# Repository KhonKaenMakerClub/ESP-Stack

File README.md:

# ESP-Stack
ESP8266 hardware and software framework

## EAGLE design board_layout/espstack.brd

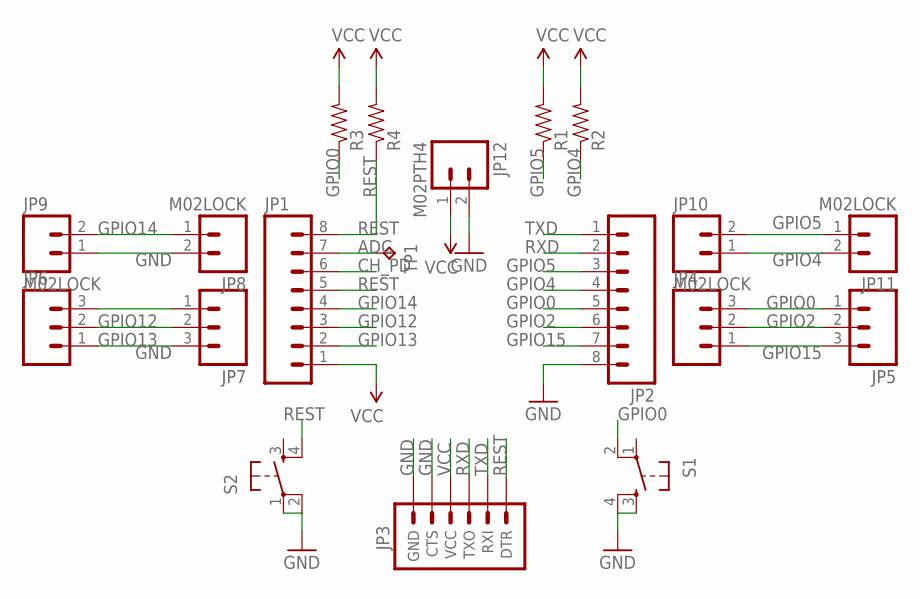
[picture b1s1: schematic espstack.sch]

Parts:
JP1, JP2: M08LOCK_LONGPADS; 1X08_LOCK_LONGPADS
JP3: ARDUINO_SERIAL_PROGRAMLOCK; 1X06_LOCK
JP4, JP5, JP6, JP7: M03LOCK; 1X03_LOCK
JP8, JP9, JP10, JP11: M02LOCK; 1X02_LOCK
JP12: M02PTH4; 1X02_XTRA_BIG
R1, R2, R3, R4: RESISTOR0805-RES; 0805
S1, S2: TAC_SWITCHPTH; TACTILE-PTH
TP1: TPB2,54; B2,54

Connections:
ADC: JP1.7, TP1.TP
CH_PD: JP1.6
GND: JP2.8, JP3.5 (CTS), JP3.6 (GND), JP6.1, JP7.3, JP8.2, JP9.1, JP12.2, S1.3, S1.4, S2.1, S2.2
GPIO0: JP2.5, JP4.3, JP5.1, R3.1, S1.2
GPIO2: JP2.6, JP4.2, JP5.2
GPIO4: JP2.4, JP10.1, JP11.2, R2.1
GPIO5: JP2.3, JP10.2, JP11.1, R1.1
GPIO12: JP1.3, JP6.3, JP7.1
GPIO13: JP1.2, JP6.2, JP7.2
GPIO14: JP1.4, JP8.1, JP9.2
GPIO15: JP2.7, JP4.1, JP5.3
REST: JP1.5, JP1.8, JP3.1 (DTR), R4.1, S2.4
RXD: JP2.2, JP3.3 (TXO)
TXD: JP2.1, JP3.2 (RXI)
VCC: JP1.1, JP3.4 (VCC), JP12.1, R1.2, R2.2, R3.2, R4.2

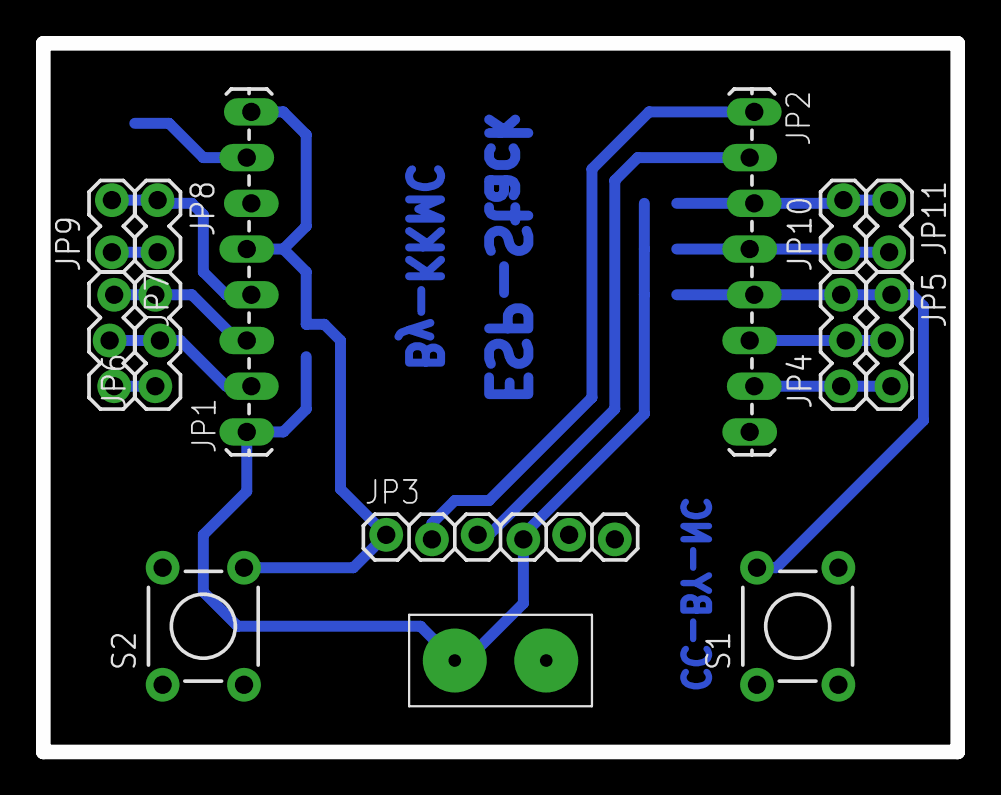
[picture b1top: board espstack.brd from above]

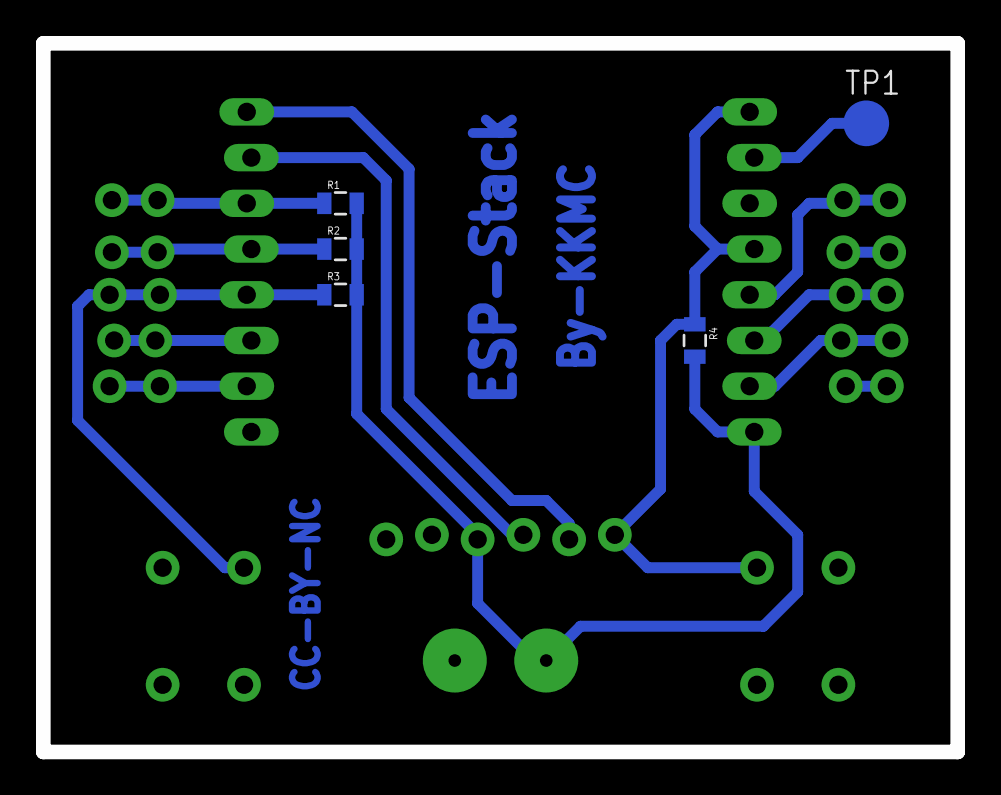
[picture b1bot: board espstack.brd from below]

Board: 2 copper layers, 50.8 x 39.4 mm, 20 parts (5 on the bottom side), 14 nets.

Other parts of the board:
U$3: A4-35SC

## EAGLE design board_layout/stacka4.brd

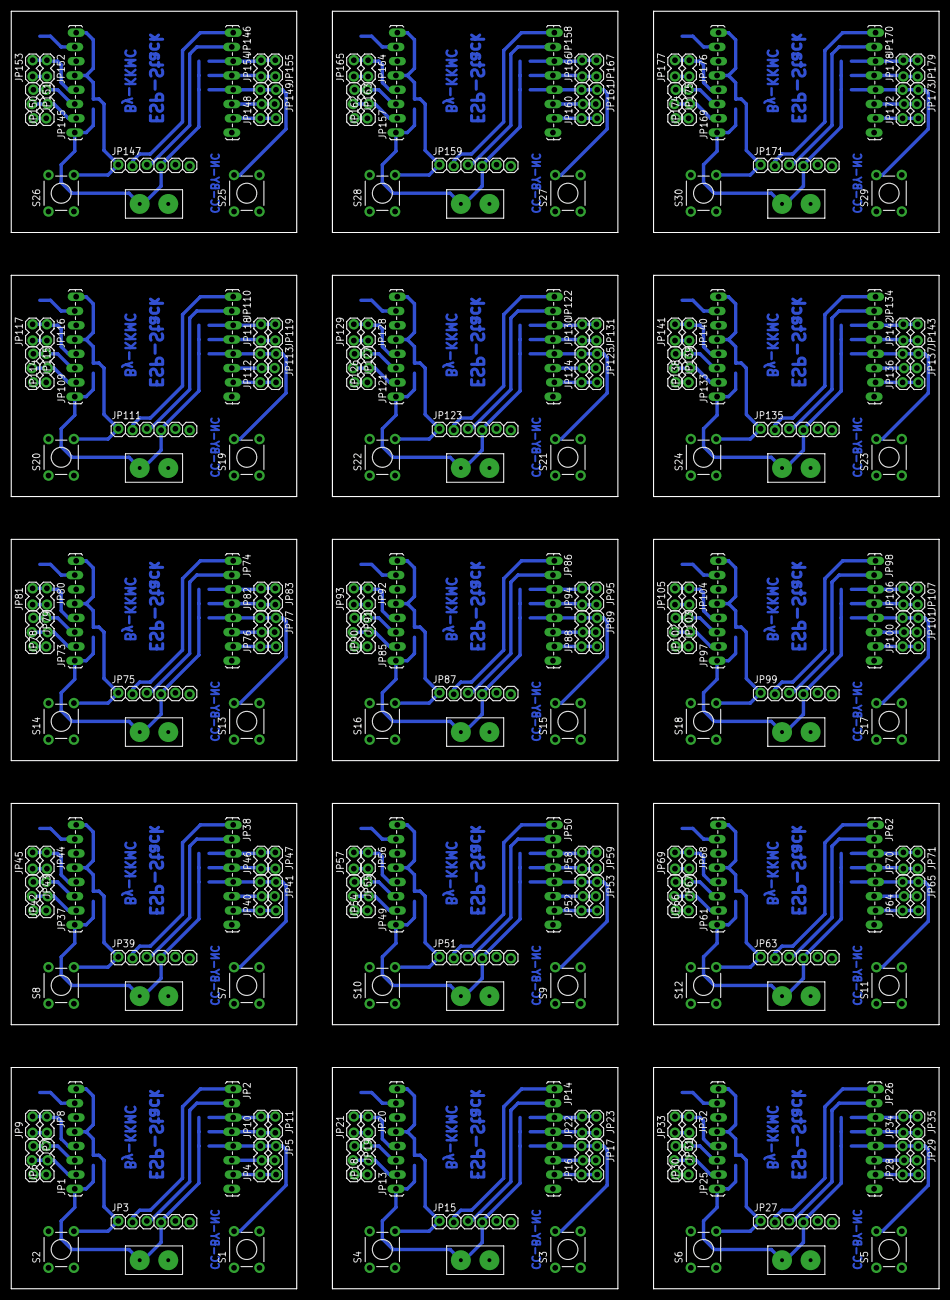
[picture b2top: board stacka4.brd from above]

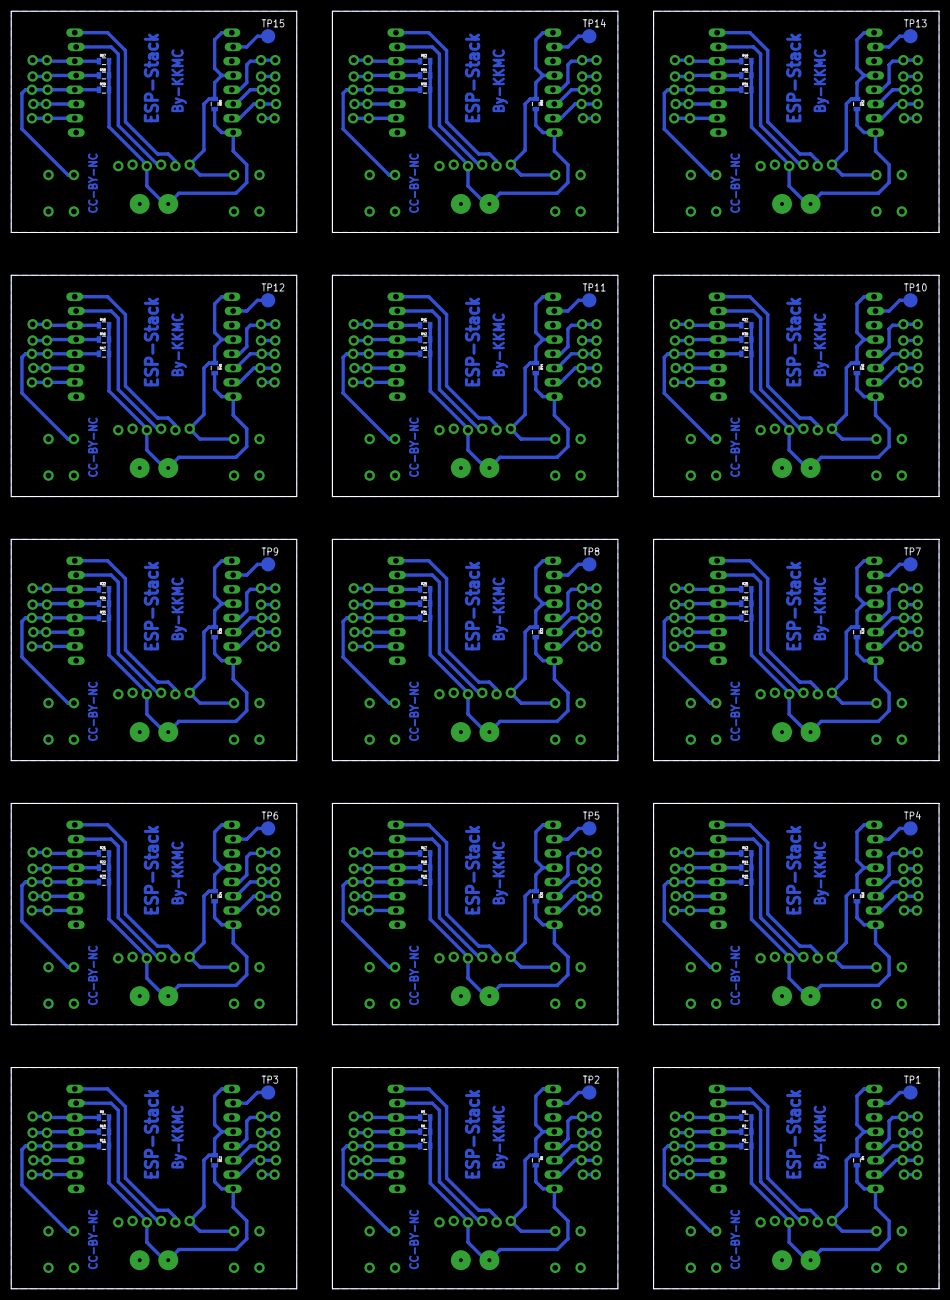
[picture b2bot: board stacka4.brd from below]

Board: 2 copper layers, 165.1 x 227.3 mm, 286 parts (75 on the bottom side), 210 nets.

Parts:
E$1: A4-35SC
JP1, JP2, JP13, JP14, JP25, JP26, JP37, JP38, JP49, JP50, JP61, JP62, JP73, JP74, JP85, JP86, JP97, JP98, JP109, JP110, JP121, JP122, JP133, JP134, JP145, JP146, JP157, JP158, JP169, JP170: 1X08_LOCK_LONGPADS
JP3, JP15, JP27, JP39, JP51, JP63, JP75, JP87, JP99, JP111, JP123, JP135, JP147, JP159, JP171: 1X06_LOCK
JP4, JP5, JP6, JP7, JP16, JP17, JP18, JP19, JP28, JP29, JP30, JP31, JP40, JP41, JP42, JP43, JP52, JP53, JP54, JP55, JP64, JP65, JP66, JP67, JP76, JP77, JP78, JP79, JP88, JP89, JP90, JP91, JP100, JP101, JP102, JP103, JP112, JP113, JP114, JP115, JP124, JP125, JP126, JP127, JP136, JP137, JP138, JP139, JP148, JP149, JP150, JP151, JP160, JP161, JP162, JP163, JP172, JP173, JP174, JP175: 1X03_LOCK
JP8, JP9, JP10, JP11, JP20, JP21, JP22, JP23, JP32, JP33, JP34, JP35, JP44, JP45, JP46, JP47, JP56, JP57, JP58, JP59, JP68, JP69, JP70, JP71, JP80, JP81, JP82, JP83, JP92, JP93, JP94, JP95, JP104, JP105, JP106, JP107, JP116, JP117, JP118, JP119, JP128, JP129, JP130, JP131, JP140, JP141, JP142, JP143, JP152, JP153, JP154, JP155, JP164, JP165, JP166, JP167, JP176, JP177, JP178, JP179: M02LOCK; 1X02_LOCK
JP12, JP24, JP36, JP48, JP60, JP72, JP84, JP96, JP108, JP120, JP132, JP144, JP156, JP168, JP180: M02PTH4; 1X02_XTRA_BIG
R1, R2, R3, R4, R5, R6, R7, R8, R9, R10, R11, R12, R13, R14, R15, R16, R17, R18, R19, R20, R21, R22, R23, R24, R25, R26, R27, R28, R29, R30, R31, R32, R33, R34, R35, R36, R37, R38, R39, R40, R41, R42, R43, R44, R45, R46, R47, R48, R49, R50, R51, R52, R53, R54, R55, R56, R57, R58, R59, R60: 0805
S1, S2, S3, S4, S5, S6, S7, S8, S9, S10, S11, S12, S13, S14, S15, S16, S17, S18, S19, S20, S21, S22, S23, S24, S25, S26, S27, S28, S29, S30: TACTILE-PTH
TP1, TP2, TP3, TP4, TP5, TP6, TP7, TP8, TP9, TP10, TP11, TP12, TP13, TP14, TP15: TPB2,54; B2,54

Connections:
ADC: JP1.7, TP1.TP
ADC1: JP13.7, TP2.TP
ADC2: JP25.7, TP3.TP
ADC3: JP37.7, TP4.TP
ADC4: JP49.7, TP5.TP
ADC5: JP61.7, TP6.TP
ADC6: JP73.7, TP7.TP
ADC7: JP85.7, TP8.TP
ADC8: JP97.7, TP9.TP
ADC9: JP109.7, TP10.TP
ADC10: JP121.7, TP11.TP
ADC11: JP133.7, TP12.TP
ADC12: JP145.7, TP13.TP
ADC13: JP157.7, TP14.TP
ADC14: JP169.7, TP15.TP
GND: JP2.8, JP3.5, JP3.6, JP6.1, JP7.3, JP8.2, JP9.1, JP12.2, S1.3, S1.4, S2.1, S2.2
GND1: JP14.8, JP15.5, JP15.6, JP18.1, JP19.3, JP20.2, JP21.1, JP24.2, S3.3, S3.4, S4.1, S4.2
GND2: JP26.8, JP27.5, JP27.6, JP30.1, JP31.3, JP32.2, JP33.1, JP36.2, S5.3, S5.4, S6.1, S6.2
GND3: JP38.8, JP39.5, JP39.6, JP42.1, JP43.3, JP44.2, JP45.1, JP48.2, S7.3, S7.4, S8.1, S8.2
GND4: JP50.8, JP51.5, JP51.6, JP54.1, JP55.3, JP56.2, JP57.1, JP60.2, S9.3, S9.4, S10.1, S10.2
GND5: JP62.8, JP63.5, JP63.6, JP66.1, JP67.3, JP68.2, JP69.1, JP72.2, S11.3, S11.4, S12.1, S12.2
GND6: JP74.8, JP75.5, JP75.6, JP78.1, JP79.3, JP80.2, JP81.1, JP84.2, S13.3, S13.4, S14.1, S14.2
GND7: JP86.8, JP87.5, JP87.6, JP90.1, JP91.3, JP92.2, JP93.1, JP96.2, S15.3, S15.4, S16.1, S16.2
GND8: JP98.8, JP99.5, JP99.6, JP102.1, JP103.3, JP104.2, JP105.1, JP108.2, S17.3, S17.4, S18.1, S18.2
GND9: JP110.8, JP111.5, JP111.6, JP114.1, JP115.3, JP116.2, JP117.1, JP120.2, S19.3, S19.4, S20.1, S20.2
GND10: JP122.8, JP123.5, JP123.6, JP126.1, JP127.3, JP128.2, JP129.1, JP132.2, S21.3, S21.4, S22.1, S22.2
GND11: JP134.8, JP135.5, JP135.6, JP138.1, JP139.3, JP140.2, JP141.1, JP144.2, S23.3, S23.4, S24.1, S24.2
GND12: JP146.8, JP147.5, JP147.6, JP150.1, JP151.3, JP152.2, JP153.1, JP156.2, S25.3, S25.4, S26.1, S26.2
GND13: JP158.8, JP159.5, JP159.6, JP162.1, JP163.3, JP164.2, JP165.1, JP168.2, S27.3, S27.4, S28.1, S28.2
GND14: JP170.8, JP171.5, JP171.6, JP174.1, JP175.3, JP176.2, JP177.1, JP180.2, S29.3, S29.4, S30.1, S30.2
GPIO0: JP2.5, JP4.3, JP5.1, R3.1, S1.2
GPIO1: JP13.4, JP20.1, JP21.2
GPIO2: JP2.6, JP4.2, JP5.2
GPIO3: JP13.3, JP18.3, JP19.1
GPIO4: JP2.4, JP10.1, JP11.2, R2.1
GPIO5: JP2.3, JP10.2, JP11.1, R1.1
GPIO6: JP13.2, JP18.2, JP19.2
GPIO7: JP14.7, JP16.1, JP17.3
GPIO8: JP14.6, JP16.2, JP17.2
GPIO9: JP14.5, JP16.3, JP17.1, R7.1, S3.2
GPIO10: JP14.4, JP22.1, JP23.2, R6.1
GPIO11: JP14.3, JP22.2, JP23.1, R5.1
GPIO12: JP1.3, JP6.3, JP7.1
GPIO13: JP1.2, JP6.2, JP7.2
GPIO14: JP1.4, JP8.1, JP9.2
GPIO15: JP2.7, JP4.1, JP5.3
GPIO16: JP25.4, JP32.1, JP33.2
GPIO17: JP25.3, JP30.3, JP31.1
GPIO18: JP25.2, JP30.2, JP31.2
GPIO19: JP26.7, JP28.1, JP29.3
GPIO20: JP26.6, JP28.2, JP29.2
GPIO21: JP26.5, JP28.3, JP29.1, R11.1, S5.2
GPIO22: JP26.4, JP34.1, JP35.2, R10.1
GPIO23: JP26.3, JP34.2, JP35.1, R9.1
GPIO24: JP37.4, JP44.1, JP45.2
GPIO25: JP37.3, JP42.3, JP43.1
GPIO26: JP37.2, JP42.2, JP43.2
GPIO27: JP38.7, JP40.1, JP41.3
GPIO28: JP38.6, JP40.2, JP41.2
GPIO29: JP38.5, JP40.3, JP41.1, R15.1, S7.2
GPIO30: JP38.4, JP46.1, JP47.2, R14.1
GPIO31: JP38.3, JP46.2, JP47.1, R13.1
GPIO32: JP49.4, JP56.1, JP57.2
GPIO33: JP49.3, JP54.3, JP55.1
GPIO34: JP49.2, JP54.2, JP55.2
GPIO35: JP50.7, JP52.1, JP53.3
GPIO36: JP50.6, JP52.2, JP53.2
GPIO37: JP50.5, JP52.3, JP53.1, R19.1, S9.2
GPIO38: JP50.4, JP58.1, JP59.2, R18.1
GPIO39: JP50.3, JP58.2, JP59.1, R17.1
GPIO40: JP61.4, JP68.1, JP69.2
GPIO41: JP61.3, JP66.3, JP67.1
GPIO42: JP61.2, JP66.2, JP67.2
GPIO43: JP62.7, JP64.1, JP65.3
GPIO44: JP62.6, JP64.2, JP65.2
GPIO45: JP62.5, JP64.3, JP65.1, R23.1, S11.2
GPIO46: JP62.4, JP70.1, JP71.2, R22.1
GPIO47: JP62.3, JP70.2, JP71.1, R21.1
GPIO48: JP73.4, JP80.1, JP81.2
GPIO49: JP73.3, JP78.3, JP79.1
GPIO50: JP73.2, JP78.2, JP79.2
GPIO51: JP74.7, JP76.1, JP77.3
GPIO52: JP74.6, JP76.2, JP77.2
GPIO53: JP74.5, JP76.3, JP77.1, R27.1, S13.2
GPIO54: JP74.4, JP82.1, JP83.2, R26.1
GPIO55: JP74.3, JP82.2, JP83.1, R25.1
GPIO56: JP85.4, JP92.1, JP93.2
GPIO57: JP85.3, JP90.3, JP91.1
GPIO58: JP85.2, JP90.2, JP91.2
GPIO59: JP86.7, JP88.1, JP89.3
GPIO60: JP86.6, JP88.2, JP89.2
GPIO61: JP86.5, JP88.3, JP89.1, R31.1, S15.2
GPIO62: JP86.4, JP94.1, JP95.2, R30.1
GPIO63: JP86.3, JP94.2, JP95.1, R29.1
GPIO64: JP97.4, JP104.1, JP105.2
GPIO65: JP97.3, JP102.3, JP103.1
GPIO66: JP97.2, JP102.2, JP103.2
GPIO67: JP98.7, JP100.1, JP101.3
GPIO68: JP98.6, JP100.2, JP101.2
GPIO69: JP98.5, JP100.3, JP101.1, R35.1, S17.2
GPIO70: JP98.4, JP106.1, JP107.2, R34.1
GPIO71: JP98.3, JP106.2, JP107.1, R33.1
GPIO72: JP109.4, JP116.1, JP117.2
GPIO73: JP109.3, JP114.3, JP115.1
GPIO74: JP109.2, JP114.2, JP115.2
GPIO75: JP110.7, JP112.1, JP113.3
GPIO76: JP110.6, JP112.2, JP113.2
GPIO77: JP110.5, JP112.3, JP113.1, R39.1, S19.2
GPIO78: JP110.4, JP118.1, JP119.2, R38.1
GPIO79: JP110.3, JP118.2, JP119.1, R37.1
GPIO80: JP121.4, JP128.1, JP129.2
GPIO81: JP121.3, JP126.3, JP127.1
GPIO82: JP121.2, JP126.2, JP127.2
GPIO83: JP122.7, JP124.1, JP125.3
GPIO84: JP122.6, JP124.2, JP125.2
GPIO85: JP122.5, JP124.3, JP125.1, R43.1, S21.2
GPIO86: JP122.4, JP130.1, JP131.2, R42.1
GPIO87: JP122.3, JP130.2, JP131.1, R41.1
GPIO88: JP133.4, JP140.1, JP141.2
GPIO89: JP133.3, JP138.3, JP139.1
GPIO90: JP133.2, JP138.2, JP139.2
GPIO91: JP134.7, JP136.1, JP137.3
GPIO92: JP134.6, JP136.2, JP137.2
GPIO93: JP134.5, JP136.3, JP137.1, R47.1, S23.2
GPIO94: JP134.4, JP142.1, JP143.2, R46.1
GPIO95: JP134.3, JP142.2, JP143.1, R45.1
GPIO96: JP145.4, JP152.1, JP153.2
GPIO97: JP145.3, JP150.3, JP151.1
GPIO98: JP145.2, JP150.2, JP151.2
GPIO99: JP146.7, JP148.1, JP149.3
GPIO100: JP146.6, JP148.2, JP149.2
GPIO101: JP146.5, JP148.3, JP149.1, R51.1, S25.2
GPIO102: JP146.4, JP154.1, JP155.2, R50.1
GPIO103: JP146.3, JP154.2, JP155.1, R49.1
GPIO104: JP157.4, JP164.1, JP165.2
GPIO105: JP157.3, JP162.3, JP163.1
GPIO106: JP157.2, JP162.2, JP163.2
GPIO107: JP158.7, JP160.1, JP161.3
GPIO108: JP158.6, JP160.2, JP161.2
GPIO109: JP158.5, JP160.3, JP161.1, R55.1, S27.2
GPIO110: JP158.4, JP166.1, JP167.2, R54.1
GPIO111: JP158.3, JP166.2, JP167.1, R53.1
GPIO112: JP169.4, JP176.1, JP177.2
GPIO113: JP169.3, JP174.3, JP175.1
GPIO114: JP169.2, JP174.2, JP175.2
GPIO115: JP170.7, JP172.1, JP173.3
GPIO116: JP170.6, JP172.2, JP173.2
GPIO117: JP170.5, JP172.3, JP173.1, R59.1, S29.2
GPIO118: JP170.4, JP178.1, JP179.2, R58.1
GPIO119: JP170.3, JP178.2, JP179.1, R57.1
REST: JP1.5, JP1.8, JP3.1, R4.1, S2.4
REST1: JP13.5, JP13.8, JP15.1, R8.1, S4.4
REST2: JP25.5, JP25.8, JP27.1, R12.1, S6.4
REST3: JP37.5, JP37.8, JP39.1, R16.1, S8.4
REST4: JP49.5, JP49.8, JP51.1, R20.1, S10.4
REST5: JP61.5, JP61.8, JP63.1, R24.1, S12.4
REST6: JP73.5, JP73.8, JP75.1, R28.1, S14.4
REST7: JP85.5, JP85.8, JP87.1, R32.1, S16.4
REST8: JP97.5, JP97.8, JP99.1, R36.1, S18.4
REST9: JP109.5, JP109.8, JP111.1, R40.1, S20.4
REST10: JP121.5, JP121.8, JP123.1, R44.1, S22.4
REST11: JP133.5, JP133.8, JP135.1, R48.1, S24.4
REST12: JP145.5, JP145.8, JP147.1, R52.1, S26.4
REST13: JP157.5, JP157.8, JP159.1, R56.1, S28.4
REST14: JP169.5, JP169.8, JP171.1, R60.1, S30.4
RXD: JP2.2, JP3.3
RXD1: JP14.2, JP15.3
RXD2: JP26.2, JP27.3
RXD3: JP38.2, JP39.3
RXD4: JP50.2, JP51.3
RXD5: JP62.2, JP63.3
RXD6: JP74.2, JP75.3
RXD7: JP86.2, JP87.3
RXD8: JP98.2, JP99.3
RXD9: JP110.2, JP111.3
RXD10: JP122.2, JP123.3
RXD11: JP134.2, JP135.3
RXD12: JP146.2, JP147.3
RXD13: JP158.2, JP159.3
RXD14: JP170.2, JP171.3
TXD: JP2.1, JP3.2
TXD1: JP14.1, JP15.2
TXD2: JP26.1, JP27.2
TXD3: JP38.1, JP39.2
TXD4: JP50.1, JP51.2
TXD5: JP62.1, JP63.2
TXD6: JP74.1, JP75.2
TXD7: JP86.1, JP87.2
TXD8: JP98.1, JP99.2
TXD9: JP110.1, JP111.2
TXD10: JP122.1, JP123.2
TXD11: JP134.1, JP135.2
TXD12: JP146.1, JP147.2
TXD13: JP158.1, JP159.2
TXD14: JP170.1, JP171.2
VCC: JP1.1, JP3.4, JP12.1, R1.2, R2.2, R3.2, R4.2
VCC1: JP13.1, JP15.4, JP24.1, R5.2, R6.2, R7.2, R8.2
VCC2: JP25.1, JP27.4, JP36.1, R9.2, R10.2, R11.2, R12.2
VCC3: JP37.1, JP39.4, JP48.1, R13.2, R14.2, R15.2, R16.2
VCC4: JP49.1, JP51.4, JP60.1, R17.2, R18.2, R19.2, R20.2
VCC5: JP61.1, JP63.4, JP72.1, R21.2, R22.2, R23.2, R24.2
VCC6: JP73.1, JP75.4, JP84.1, R25.2, R26.2, R27.2, R28.2
VCC7: JP85.1, JP87.4, JP96.1, R29.2, R30.2, R31.2, R32.2
VCC8: JP97.1, JP99.4, JP108.1, R33.2, R34.2, R35.2, R36.2
VCC9: JP109.1, JP111.4, JP120.1, R37.2, R38.2, R39.2, R40.2
VCC10: JP121.1, JP123.4, JP132.1, R41.2, R42.2, R43.2, R44.2
VCC11: JP133.1, JP135.4, JP144.1, R45.2, R46.2, R47.2, R48.2
VCC12: JP145.1, JP147.4, JP156.1, R49.2, R50.2, R51.2, R52.2
VCC13: JP157.1, JP159.4, JP168.1, R53.2, R54.2, R55.2, R56.2
VCC14: JP169.1, JP171.4, JP180.1, R57.2, R58.2, R59.2, R60.2

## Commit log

2015-11-22 :boom::camel: Added .gitattributes & .gitignore files
2015-11-22 Add schematic and board layout
2015-11-27 sync with Blynk and CMMC Wificonnector
2015-12-05 Add deep sleep
2016-01-30 add plugin freeboard
2016-01-30 add css
2016-01-30 add more class
2016-01-30 Rename
2016-01-30 remove css

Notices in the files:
board_layout/espstack.brd:
CC-BY-NC
parts and their libraries:
SparkFun-Connectors: Licensing: Creative Commons ShareAlike 4.0 International - https://creativecommons.org/licenses/by-sa/4.0
